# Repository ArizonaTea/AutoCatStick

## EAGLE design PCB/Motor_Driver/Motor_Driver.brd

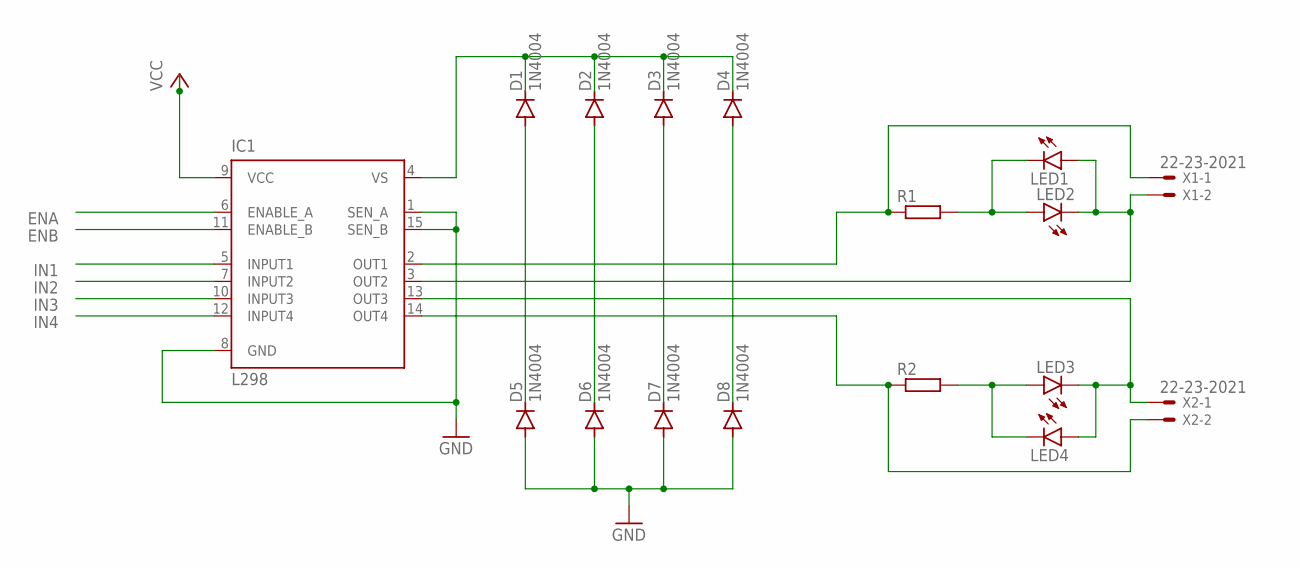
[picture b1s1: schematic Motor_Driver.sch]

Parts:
D1, D2, D3, D4, D5, D6, D7, D8: 1N4004; DO41-10
IC1: L298; MULTIWATT-15
LED1, LED2, LED3, LED4: LEDCHIP-LED0603; CHIP-LED0603
R1, R2: R-EU_R0603; R0603
X1, X2: 22-23-2021

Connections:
ENA: IC1.6 (ENABLE_A)
ENB: IC1.11 (ENABLE_B)
GND: D5.A, D6.A, D7.A, D8.A, IC1.1 (SEN_A), IC1.8 (GND), IC1.15 (SEN_B)
IN1: IC1.5 (INPUT1)
IN2: IC1.7 (INPUT2)
IN3: IC1.10 (INPUT3)
IN4: IC1.12 (INPUT4)
unnamed: D1.C, D2.C, D3.C, D4.C, IC1.4 (VS)
unnamed: D1.A, D5.C
unnamed: D2.A, D6.C
unnamed: D3.A, D7.C
unnamed: D4.A, D8.C
unnamed: IC1.2 (OUT1), R1.1, X1.1
unnamed: LED1.C, LED2.A, R1.2
unnamed: IC1.3 (OUT2), LED1.A, LED2.C, X1.2
unnamed: LED3.A, LED4.C, R2.2
unnamed: IC1.14 (OUT4), R2.1, X2.2
unnamed: IC1.13 (OUT3), LED3.C, LED4.A, X2.1
VCC: IC1.9 (VCC)

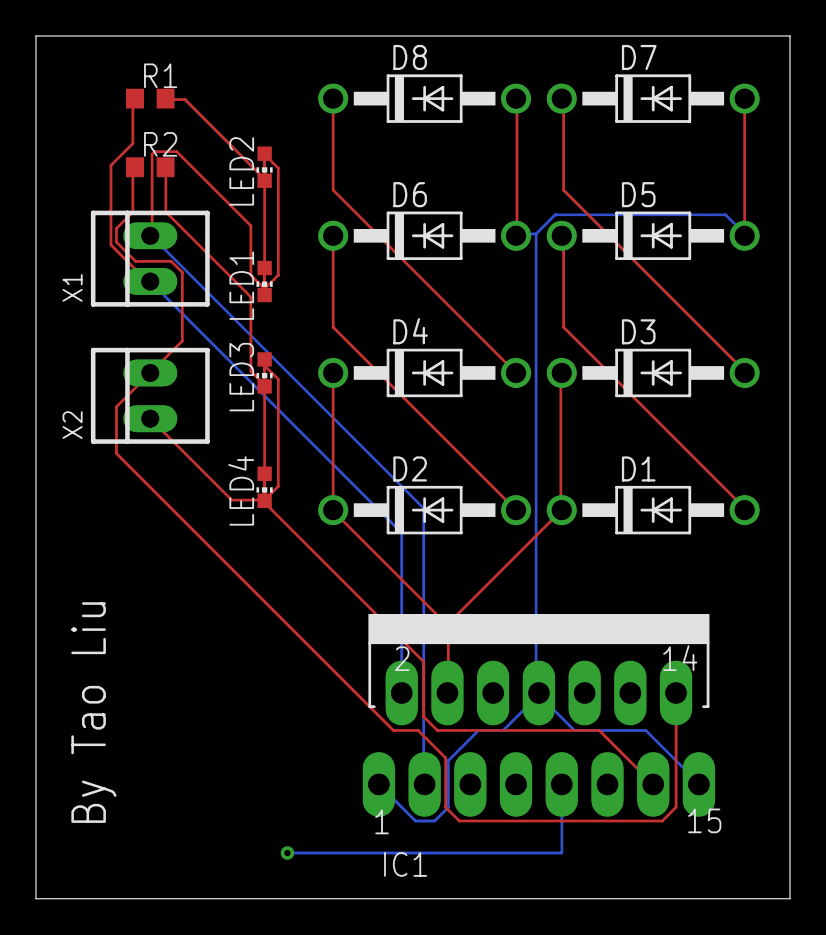
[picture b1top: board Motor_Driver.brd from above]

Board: 2 copper layers, 41.9 x 47.9 mm, 17 parts (0 on the bottom side), 12 nets.

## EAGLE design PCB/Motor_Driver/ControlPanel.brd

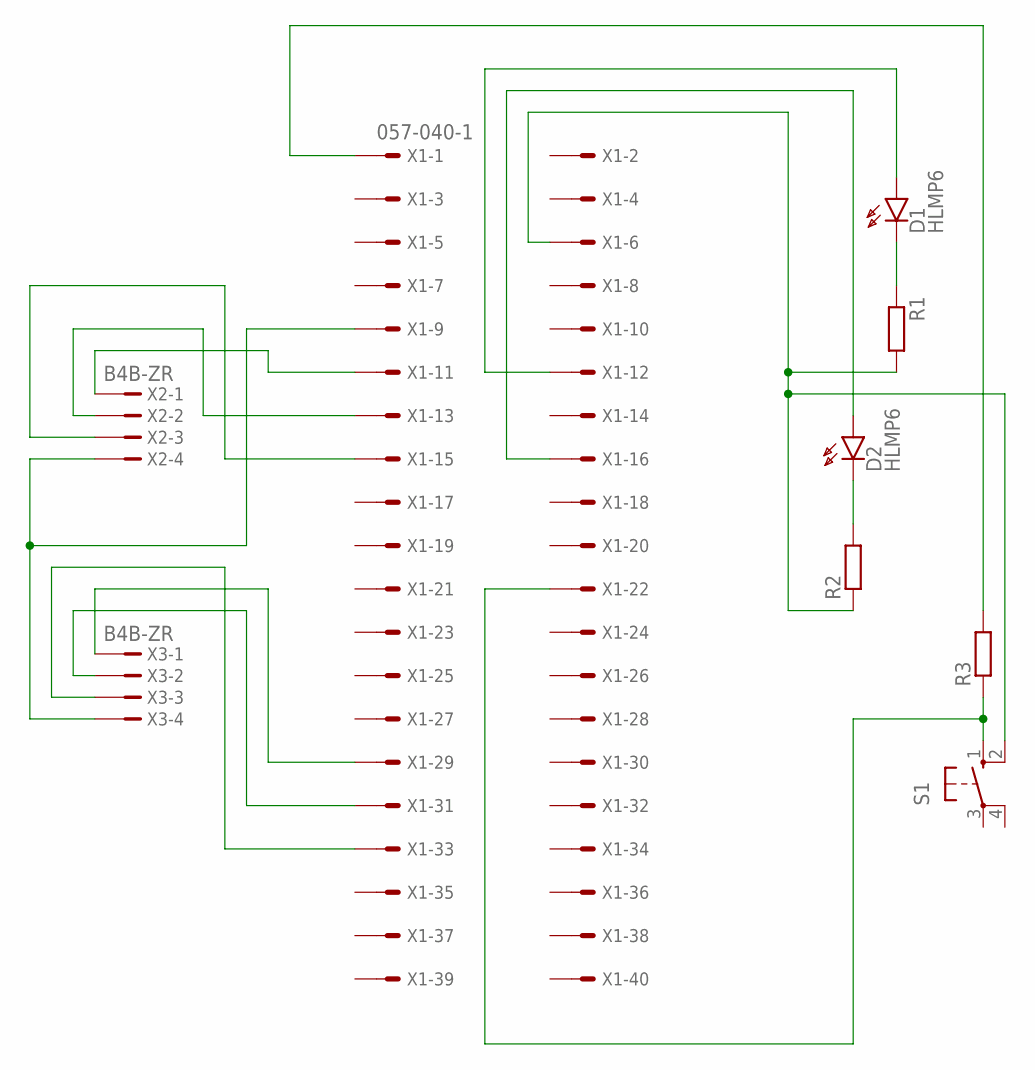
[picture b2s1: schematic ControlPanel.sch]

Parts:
D1, D2: HLMP6
R1, R2, R3: R-EU_0204/7; 0204/7
S1: 10-XX; B3F-10XX
X1: 057-040-1
X2, X3: B4B-ZR

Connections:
unnamed: D1.A, X1.12
unnamed: D2.A, X1.16
unnamed: D1.K, R1.1
unnamed: R1.2, R2.1, S1.2 (S1), X1.6
unnamed: D2.K, R2.2
unnamed: R3.2, X1.1
unnamed: R3.1, S1.1 (S), X1.22
unnamed: X1.9, X2.4, X3.4
unnamed: X1.11, X2.1
unnamed: X1.13, X2.2
unnamed: X1.15, X2.3
unnamed: X1.29, X3.1
unnamed: X1.31, X3.2
unnamed: X1.33, X3.3

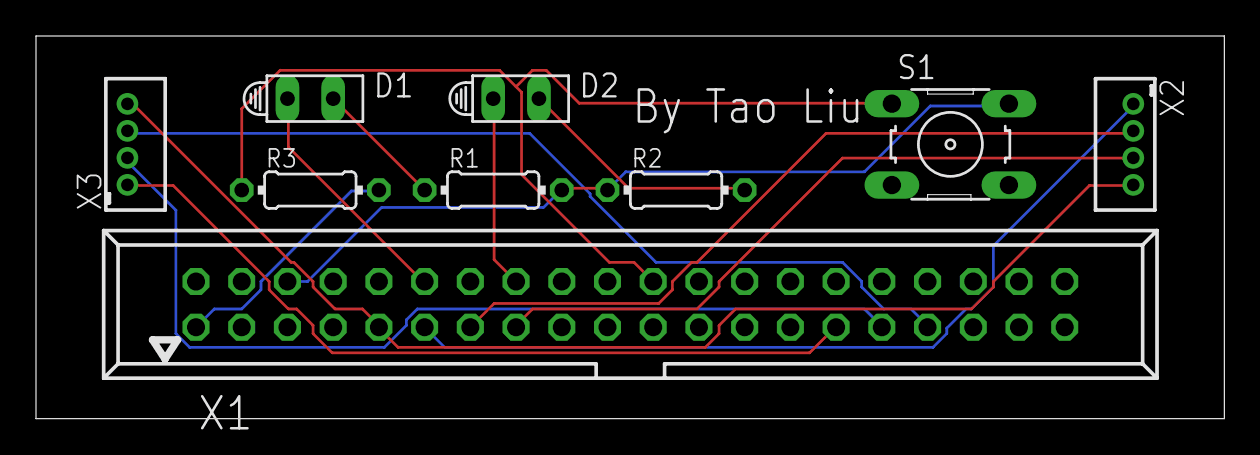
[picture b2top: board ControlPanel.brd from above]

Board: 2 copper layers, 66.0 x 21.3 mm, 9 parts (0 on the bottom side), 14 nets.

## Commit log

2021-04-05 Regular Updates
2021-04-07 Added Camera SW and Motor Driver PCB Schematic
2021-04-07 Added the PCB board and model
    Added PCB board design for motor driver, concept modeling of the machine. Still need more work.
2021-04-09 Added the main control SW. Including the complete process
2021-04-10 Finished complete Turn ON/OFF functions. Add GPIO reset script.
2021-04-12 Added 3D modeling
2021-04-13 Updated the control PCBA design
2021-04-19 Remove Smart Car content, separate project
2021-04-20 Remove the Notes part. Added the Motor related code
2021-05-03 Updated the SW draft
2021-11-09 Reorganize the folders
2021-11-10 Update the AD PCB design
2021-11-11 RegularUpdates
2021-11-24 Regular Updates. The PCB design project is finishing.
2021-11-24 Update Garber file for production
2021-11-24 Updated gerber file
2021-11-24 Updated for MFG
2022-01-01 Bug fix for the P1 V1.0 brd. Updated to P1 V1.1 brd.
2024-12-03 Main
    Updates
